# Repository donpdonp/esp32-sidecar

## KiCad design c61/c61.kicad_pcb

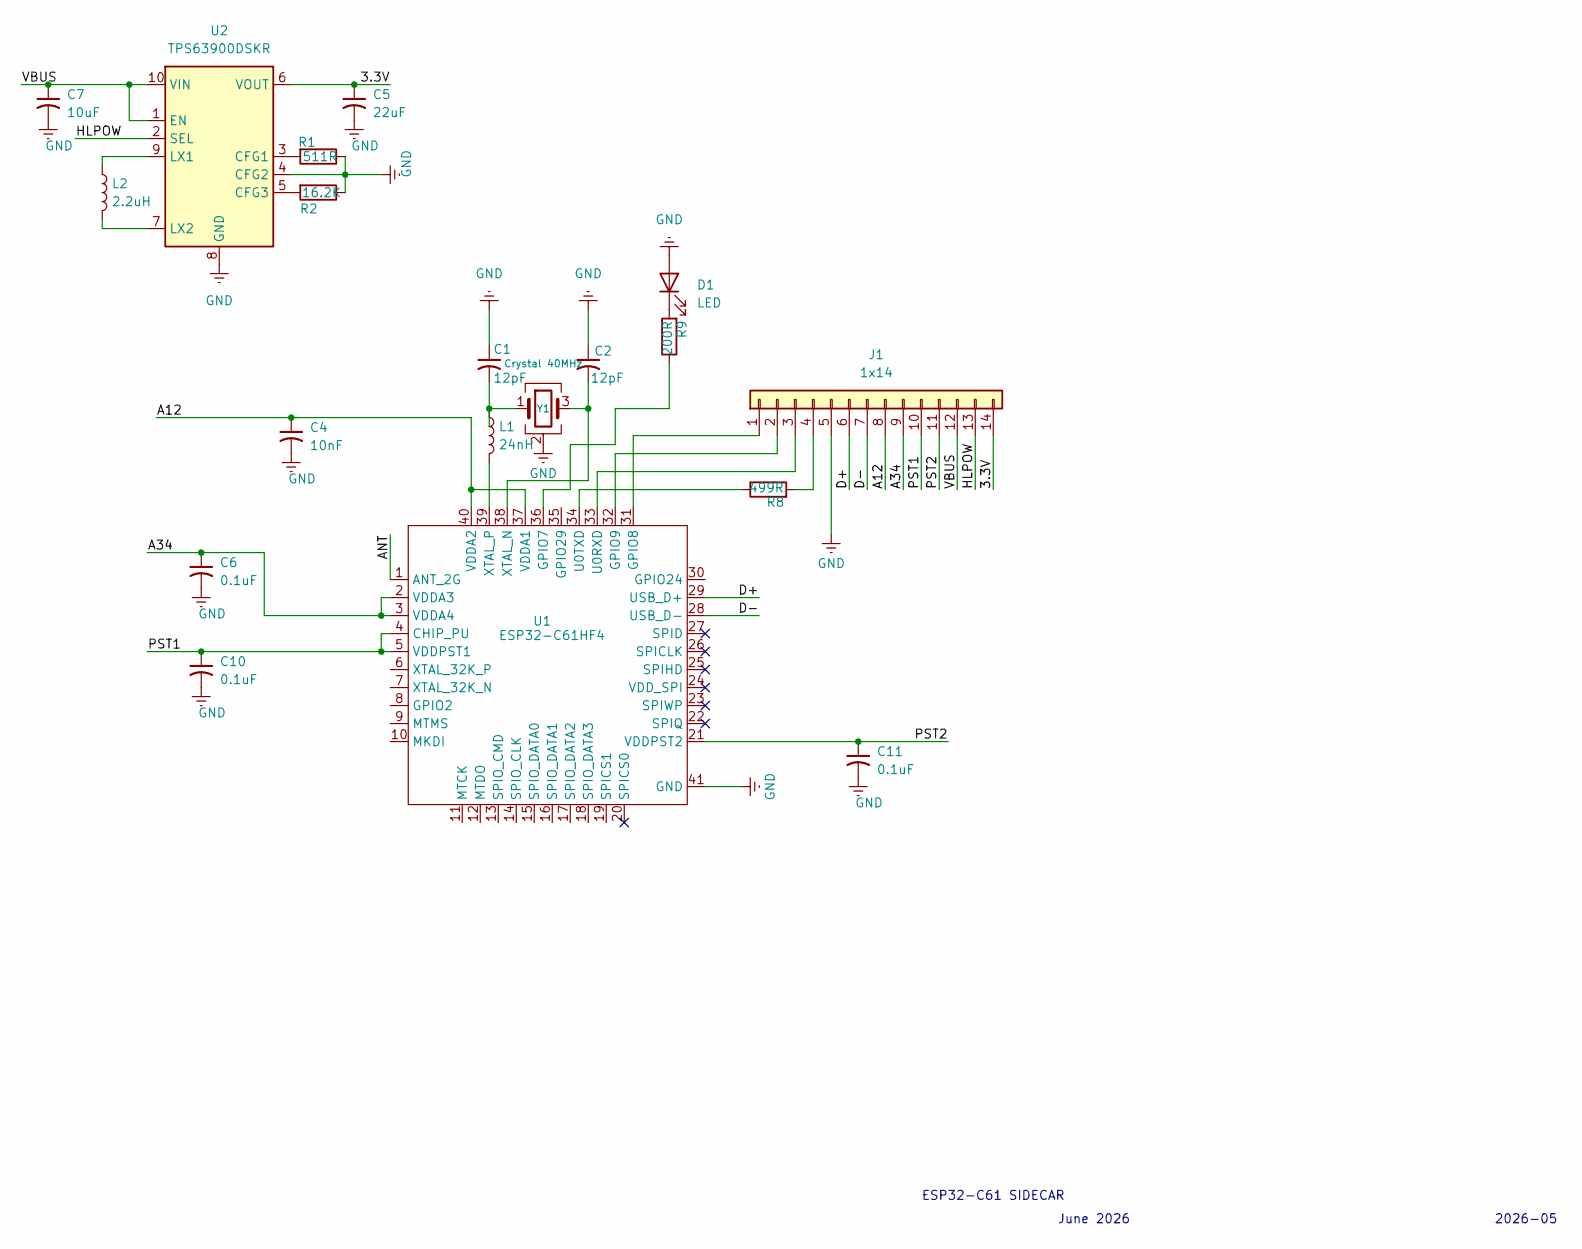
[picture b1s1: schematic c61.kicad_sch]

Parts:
C1, C2: 12pF; C_0805_2012Metric_Pad1.18x1.45mm_HandSolder
C4: 10nF; C_0805_2012Metric_Pad1.18x1.45mm_HandSolder
C5: 22uF; C_0805_2012Metric_Pad1.18x1.45mm_HandSolder
C6, C10, C11: 0.1uF; C_0805_2012Metric_Pad1.18x1.45mm_HandSolder
C7: 10uF; C_0805_2012Metric_Pad1.18x1.45mm_HandSolder
D1: LED; LED_1206_3216Metric
J1: 1x14; PinHeader_1x14_P2.54mm_Vertical
L1: 24nH; L_0603_1608Metric_Pad1.05x0.95mm_HandSolder
L2: 2.2uH; L_0603_1608Metric_Pad1.05x0.95mm_HandSolder
R1: 511R; R_0805_2012Metric_Pad1.20x1.40mm_HandSolder
R2: 16.2K; R_0805_2012Metric_Pad1.20x1.40mm_HandSolder
R8: 499R; R_0603_1608Metric_Pad0.98x0.95mm_HandSolder
R9: 200R; R_0603_1608Metric_Pad0.98x0.95mm_HandSolder
U1: ESP32-C61HF4; QFN-40-1EP_5x5mm_P0.4mm_EP3.6x3.6mm
U2: TPS63900DSKR; WSON-10-1EP_2.5x2.5mm_P0.5mm_EP1.2x2mm_ThermalVias
Y1: Crystal 40MHz; Crystal_SMD_3225-4Pin_3.2x2.5mm

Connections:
/3.3V: C5.1, J1.14, U2.6 (VOUT)
/A12: C4.1, J1.8, U1.37 (VDDA1), U1.40 (VDDA2)
/A34: C6.1, J1.9, U1.2 (VDDA3), U1.3 (VDDA4)
/ANT: U1.1 (ANT_2G); also elsewhere on the board
/D+: J1.6, U1.29 (USB_D+)
/D-: J1.7, U1.28 (USB_D-)
/HLPOW: J1.13, U2.2 (SEL)
/PST1: C10.1, J1.10, U1.4 (CHIP_PU), U1.5 (VDDPST1)
/PST2: C11.1, J1.11, U1.21 (VDDPST2)
/VBUS: C7.1, J1.12, U2.1 (EN), U2.10 (VIN)
GND: C1.1, C2.1, C4.2, C5.2, C6.2, C7.2, C10.2, C11.2, D1.2 (A), J1.5, R1.1, R2.1, U1.41 (GND), U2.4 (CFG2), U2.8 (GND), U2.11 (GND), Y1.2 (G), Y1.4 (G); also elsewhere on the board
unnamed: C1.2, L1.1, Y1.1
unnamed: D1.1 (K), R9.2
unnamed: J1.1, U1.31 (GPIO8)
unnamed: J1.2, U1.32 (GPIO9)
unnamed: J1.3, U1.33 (U0RXD)
unnamed: J1.4, R8.2
unnamed: R9.1, U1.36 (GPIO7)
unnamed: R8.1, U1.34 (U0TXD)
unnamed: C2.2, U1.38 (XTAL_N), Y1.3
unnamed: L1.2, U1.39 (XTAL_P)
unnamed: R1.2, U2.3 (CFG1)
unnamed: R2.2, U2.5 (CFG3)
unnamed: L2.1, U2.9 (LX1)
unnamed: L2.2, U2.7 (LX2)

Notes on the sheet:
2026-05
ESP32-C61 SIDECAR
June 2026

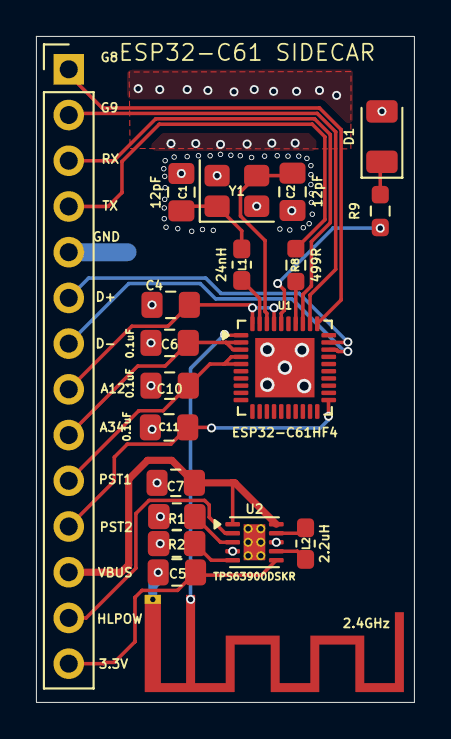
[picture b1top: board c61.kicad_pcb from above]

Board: 2 copper layers, 21.0 x 37.0 mm, 20 parts (0 on the bottom side), 25 nets.

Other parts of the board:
2.4GHz: SWRA117D_2.4GHz; Texas_SWRA117D_2.4GHz_Left

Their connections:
/ANT: 2.4GHz.1; also elsewhere on the board
GND: 2.4GHz.2; also elsewhere on the board

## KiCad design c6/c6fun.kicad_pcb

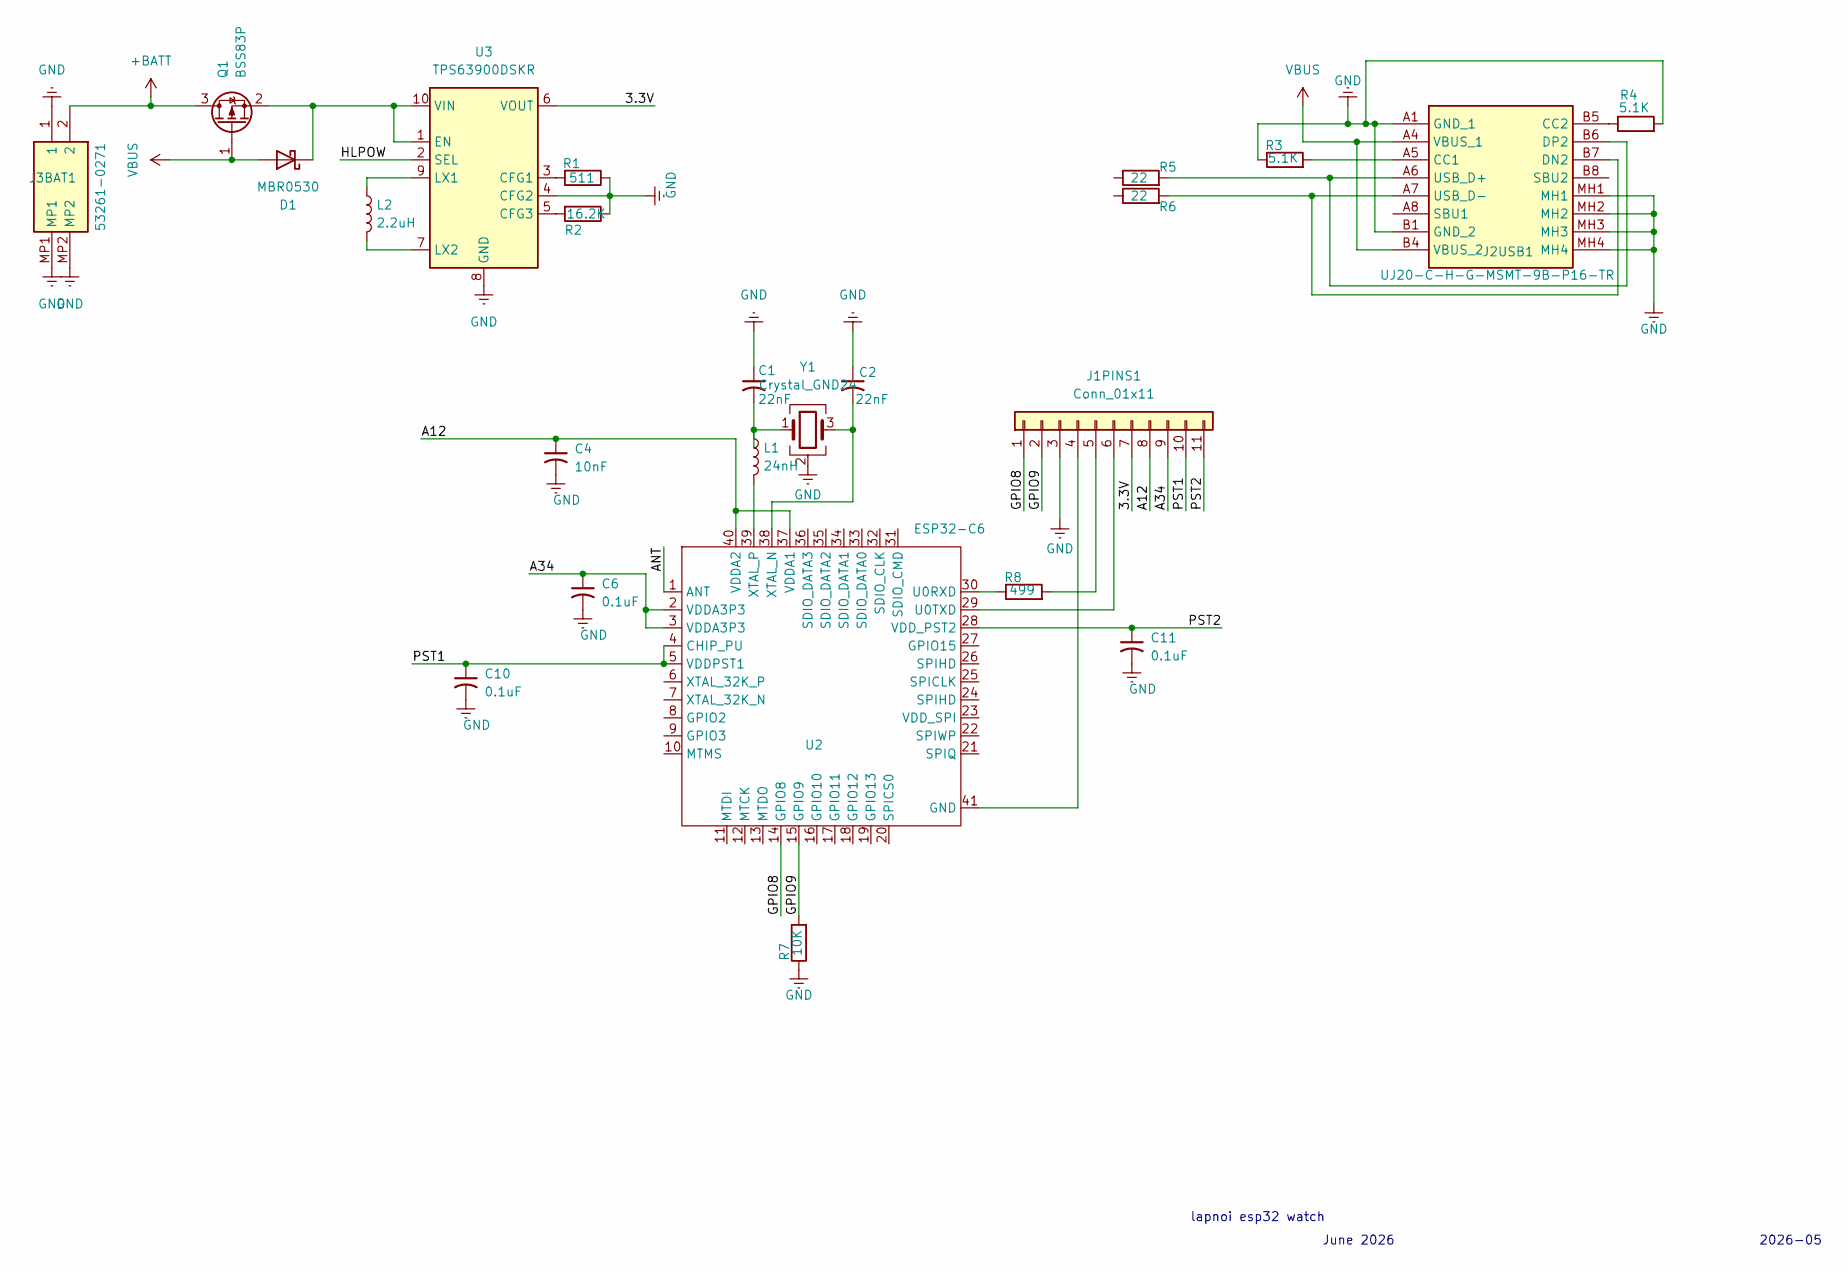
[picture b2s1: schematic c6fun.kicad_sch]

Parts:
C1, C2: 22nF; C_0805_2012Metric_Pad1.18x1.45mm_HandSolder
C4: 10nF; C_0603_1608Metric_Pad1.08x0.95mm_HandSolder
C6, C10, C11: 0.1uF; C_0805_2012Metric_Pad1.18x1.45mm_HandSolder
D1: MBR0530; D_SOD-123
J1PINS1: Conn_01x11; PinHeader_1x11_P1.00mm_Vertical
J2USB1: UJ20-C-H-G-MSMT-9B-P16-TR; UJ20CHGMSMT9BP16TR; Manufacturer_Part_Number UJ20-C-H-G-MSMT-9B-P16-TR
J3BAT1: 53261-0271; Molex_PicoBlade_53261-0271_1x02-1MP_P1.25mm_Horizontal; Mouser Part Number 538-53261-0271
L1: 24nH; L_0603_1608Metric_Pad1.05x0.95mm_HandSolder
L2: 2.2uH; L_0603_1608Metric_Pad1.05x0.95mm_HandSolder
Q1: BSS83P; SOT-23
R1: 511; R_0603_1608Metric_Pad0.98x0.95mm_HandSolder
R2: 16.2K; R_0603_1608Metric_Pad0.98x0.95mm_HandSolder
R3, R4: 5.1K; R_0603_1608Metric_Pad0.98x0.95mm_HandSolder
R5, R6: 22; R_0603_1608Metric_Pad0.98x0.95mm_HandSolder
R7: 10K; R_0603_1608Metric_Pad0.98x0.95mm_HandSolder
R8: 499; R_0603_1608Metric_Pad0.98x0.95mm_HandSolder
U2: ESP32-C6; QFN-40-1EP_5x5mm_P0.4mm_EP3.6x3.6mm
U3: TPS63900DSKR; WSON-10-1EP_2.5x2.5mm_P0.5mm_EP1.2x2mm_ThermalVias
Y1: Crystal_GND24; Crystal_SMD_3225-4Pin_3.2x2.5mm_HandSoldering

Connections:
+BATT: J3BAT1.2, Q1.3 (D)
/3.3V: J1PINS1.7, U3.6 (VOUT)
/A12: C4.1, J1PINS1.8, U2.37 (VDDA1), U2.40 (VDDA2)
/A34: C6.1, J1PINS1.9, U2.2 (VDDA3P3), U2.3 (VDDA3P3)
/ANT: U2.1 (ANT)
/GPIO8: J1PINS1.1, U2.14 (GPIO8)
/GPIO9: J1PINS1.2, R7.2, U2.15 (GPIO9)
/HLPOW: U3.2 (SEL)
/PST1: C10.1, J1PINS1.10, U2.4 (CHIP_PU), U2.5 (VDDPST1)
/PST2: C11.1, J1PINS1.11, U2.28 (VDD_PST2)
GND: C1.1, C2.1, C4.2, C6.2, C10.2, C11.2, J1PINS1.3, J2USB1.A1 (GND_1), J2USB1.B1 (GND_2), J2USB1.MH1, J2USB1.MH2, J2USB1.MH3, J2USB1.MH4, J3BAT1.1, J3BAT1.MP1, J3BAT1.MP2, R1.1, R2.1, R3.1, R4.2, R7.1, U3.4 (CFG2), U3.8 (GND), U3.11 (GND), Y1.2 (G), Y1.4 (G)
unnamed: C1.2, L1.1, Y1.1
unnamed: D1.1 (K), Q1.2 (S), U3.1 (EN), U3.10 (VIN)
unnamed: J1PINS1.4, U2.41 (GND)
unnamed: J1PINS1.5, R8.2
unnamed: J1PINS1.6, U2.29 (U0TXD)
unnamed: J2USB1.A5 (CC1), R3.2
unnamed: J2USB1.B5 (CC2), R4.1
unnamed: J2USB1.A7 (USB_D-), J2USB1.B7 (DN2), R6.2
unnamed: J2USB1.A6 (USB_D+), J2USB1.B6 (DP2), R5.2
unnamed: R8.1, U2.30 (U0RXD)
unnamed: C2.2, U2.38 (XTAL_N), Y1.3
unnamed: L1.2, U2.39 (XTAL_P)
unnamed: R1.2, U3.3 (CFG1)
unnamed: R2.2, U3.5 (CFG3)
unnamed: L2.1, U3.9 (LX1)
unnamed: L2.2, U3.7 (LX2)
VBUS: D1.2 (A), J2USB1.A4 (VBUS_1), J2USB1.B4 (VBUS_2), Q1.1 (G)

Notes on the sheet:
2026-05
lapnoi esp32 watch
June 2026

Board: 2 copper layers, 22 parts (0 on the bottom side), 21 nets, no tracks yet.
